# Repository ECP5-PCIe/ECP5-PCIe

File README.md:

# ECP5-PCIe

## ECP5 to PCIe interface development

The goal of this project is to provide a PCIe interface in [Amaranth HDL](https://github.com/amaranth-lang/amaranth).

## Previous work

There already exists a PCIe physical layer by whitequark called [Yumewatari](https://github.com/whitequark/Yumewatari) and a TLP and DMA layer by enjoy-digital called [litepcie](https://github.com/enjoy-digital/litepcie/tree/master/litepcie) written in omigen.

## TODO
- Read through Yumewatari and litepcie code
- Read more of the PCIe spec and summarize relevant parts
- Get an ECP5 device capable of PCIe
	- Currently an adapter for the ECP5 EVN to PCIe is being built

## INSTALL

Execute `python setup.py develop` in the Gateware folder

## SIMULATE

- Execute `python test_pcie_virtual.py` in the Tests folder to run the simulation
- Execute `gtkwave test.gtkw` to view the results

## [SETUP][wiki-setup]

See [the Setup page in the Wiki][wiki-setup]

## RUN

- Enable PCIe on the connected device (for example on the ROCKPro64 execute `pci init` in u-boot)
- Execute `python test_pcie_phy.py run` in the Tests folder to upload the gateware to the ECP5
- Execute `python test_pcie_phy.py grab` to get DLLPs received in the L0 state (and the time since it has been in the L0 state).
Sometimes the last few results are invalid and the program doesn't halt, end it by pressing `Ctrl + C`.
It should show something like this:

Data is composed of the first symbol received in one clock cycle, its representation in hexadecimal, the same for the second symbol.
The time is in clock cycles since entering L0, which are 8 ns each.

#### Time since L0 | RX data | TX data | Temperature

[wiki-setup]: https://codeberg.org/ECP5-PCIe/ECP5-PCIe/wiki/Setup

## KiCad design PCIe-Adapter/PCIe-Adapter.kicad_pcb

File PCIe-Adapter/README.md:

# ECP5 EVN to PCIe x4 adapter board
This is an adapter board for the ECP5 EVN, such that it can be used with PCIe x1 or x4. It has a PLL to double the incoming PCIe clock, since it has better jitter performance than the ones in the ECP5.
It also has an ATMega328 which is connected over UART to the ECP5 to save on interface pins and FPGA logic complexity for configuring the PLL.

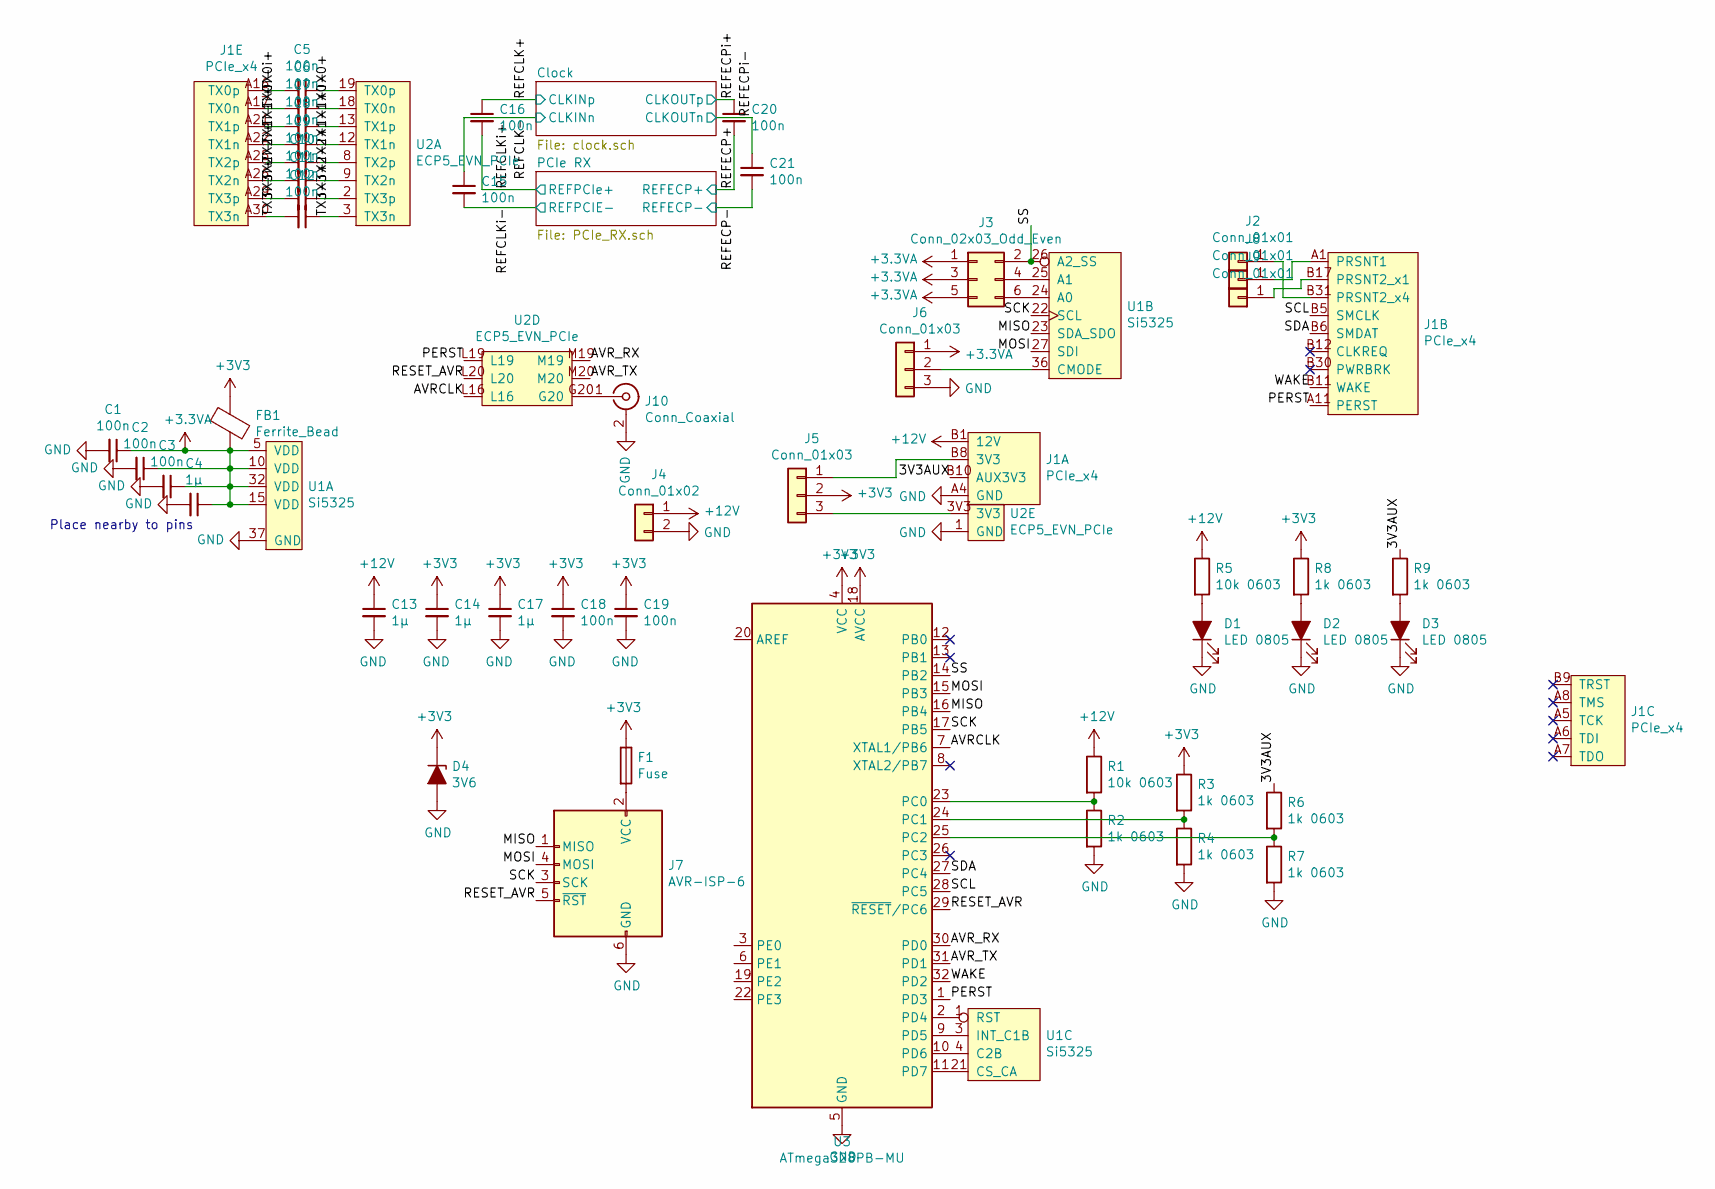
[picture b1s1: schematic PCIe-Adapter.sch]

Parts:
C1, C2, C3, C5, C6, C7, C8, C9, C10, C11, C12, C15, C16, C18, C19, C20, C21: 100n; C_0402_1005Metric
C4, C13, C14, C17: 1µ; C_0805_2012Metric
D1, D2, D3: LED 0805; LED_0805_2012Metric
D4: 3V6; D_SMB
F1: Fuse; Fuse_1206_3216Metric
FB1: Ferrite_Bead; L_0805_2012Metric
J1: PCIe_x4
J2, J8, J9: Conn_01x01; TestPoint_Pad_1.5x1.5mm
J3: Conn_02x03_Odd_Even; PinHeader_2x03_P2.54mm_Vertical
J4: Conn_01x02; PinHeader_1x02_P2.54mm_Vertical
J5, J6: Conn_01x03; PinHeader_1x03_P2.54mm_Vertical
J7: AVR-ISP-6; PinHeader_2x03_P2.54mm_Vertical
J10: Conn_Coaxial; SMA_Samtec_SMA-J-P-X-ST-EM1_EdgeMount
R1, R5: 10k 0603; R_0603_1608Metric
R2, R3, R4, R6, R7, R8, R9: 1k 0603; R_0603_1608Metric
U1: Si5325
U2: ECP5_EVN_PCIe; ECP5-EVN-PCIe
U3: ATmega328PB-MU; QFN-32-1EP_5x5mm_P0.5mm_EP3.1x3.1mm

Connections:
+3.3VA: C1.1, C2.1, C3.1, C4.1, FB1.2, J3.1, J3.3, J3.5, J6.1, U1.5 (VDD), U1.10 (VDD), U1.11 (VDD), U1.15 (VDD), U1.32 (VDD)
+3V3: C14.1, C17.1, C18.1, C19.1, D4.1 (K), F1.1, FB1.1, J5.2, R3.1, R8.1, U3.4 (VCC), U3.18 (AVCC)
+12V: C13.1, J1.A2 (12V), J1.A3 (12V), J1.B1 (12V), J1.B2 (12V), J1.B3 (12V), J4.1, R1.1, R5.1
/3V3AUX: J1.B10 (AUX3V3), R6.1, R9.1
/AVRCLK: U2.L16, U3.7 (XTAL1/PB6)
/AVR_RX: U2.M19, U3.30 (PD0)
/AVR_TX: U2.M20, U3.31 (PD1)
/MISO: J7.1 (MISO), U1.23 (SDA_SDO), U3.16 (PB4)
/MOSI: J7.4 (MOSI), U1.27 (SDI), U3.15 (PB3)
/PERST: J1.A11 (PERST), U2.L19, U3.1 (PD3)
/REFCLK+: C16.1; also elsewhere on the board
/REFCLK-: C15.1; also elsewhere on the board
/REFCLKi+: C16.2; also elsewhere on the board
/REFCLKi-: C15.2; also elsewhere on the board
/REFECP+: C20.2; also elsewhere on the board
/REFECP-: C21.2; also elsewhere on the board
/REFECPi+: C20.1; also elsewhere on the board
/REFECPi-: C21.1; also elsewhere on the board
/RESET_AVR: J7.5 (~RST), U2.L20, U3.29 (~RESET~/PC6)
/SCK: J7.3 (SCK), U1.22 (SCL), U3.17 (PB5)
/SCL: J1.B5 (SMCLK), U3.28 (PC5)
/SDA: J1.B6 (SMDAT), U3.27 (PC4)
/SS: J3.2, U1.26 (A2_SS), U3.14 (PB2)
/TX0+: C5.1, U2.19 (TX0p)
/TX0-: C6.1, U2.18 (TX0n)
/TX0i+: C5.2, J1.A16 (TX0p)
/TX0i-: C6.2, J1.A17 (TX0n)
/TX1+: C7.1, U2.13 (TX1p)
/TX1-: C8.1, U2.12 (TX1n)
/TX1i+: C7.2, J1.A21 (TX1p)
/TX1i-: C8.2, J1.A22 (TX1n)
/TX2+: C9.1, U2.8 (TX2p)
/TX2-: C10.1, U2.9 (TX2n)
/TX2i+: C9.2, J1.A25 (TX2p)
/TX2i-: C10.2, J1.A26 (TX2n)
/TX3+: C11.1, U2.2 (TX3p)
/TX3-: C12.1, U2.3 (TX3n)
/TX3i+: C11.2, J1.A29 (TX3p)
/TX3i-: C12.2, J1.A30 (TX3n)
/WAKE: J1.B11 (WAKE), U3.32 (PD2)
GND: C1.2, C2.2, C3.2, C4.2, C13.2, C14.2, C17.2, C18.2, C19.2, D1.1 (K), D2.1 (K), D3.1 (K), D4.2 (A), J1.A4 (GND), J1.A12 (GND), J1.A15 (GND), J1.A18 (GND), J1.A20 (GND), J1.A23 (GND), J1.A24 (GND), J1.A27 (GND), J1.A28 (GND), J1.A31 (GND), J1.B4 (GND), J1.B7 (GND), J1.B13 (GND), J1.B16 (GND), J1.B18 (GND), J1.B21 (GND), J1.B22 (GND), J1.B25 (GND), J1.B26 (GND), J1.B29 (GND), J1.B32 (GND), J4.2, J6.3, J7.6 (GND), J10.2 (Ext), R2.2, R4.2, R7.2, U1.6 (GND), U1.8 (GND), U1.19 (GND), U1.20 (GND), U1.31 (GND), U1.37 (GND), U2.1 (GND), U3.5 (GND), U3.21 (GND), U3.33 (GND)
unnamed: D1.2 (A), R5.2
unnamed: D2.2 (A), R8.2
unnamed: D3.2 (A), R9.2
unnamed: F1.2, J7.2 (VCC)
unnamed: J1.A1 (PRSNT1), J8.1
unnamed: J1.A9 (3V3), J1.A10 (3V3), J1.B8 (3V3), J5.1
unnamed: J1.B17 (PRSNT2_x1), J9.1
unnamed: J1.B31 (PRSNT2_x4), J2.1
unnamed: J3.4, U1.25 (A1)
unnamed: J3.6, U1.24 (A0)
unnamed: J5.3, U2.3V3
unnamed: J6.2, U1.36 (CMODE)
unnamed: J10.1 (In), U2.G20
unnamed: R1.2, R2.1, U3.23 (PC0)
unnamed: R3.2, R4.1, U3.24 (PC1)
unnamed: R6.2, R7.1, U3.25 (PC2)
unnamed: U1.1 (RST), U3.2 (PD4)
unnamed: U1.3 (INT_C1B), U3.9 (PD5)
unnamed: U1.4 (C2B), U3.10 (PD6)
unnamed: U1.21 (CS_CA), U3.11 (PD7)

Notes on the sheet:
Place nearby to pins

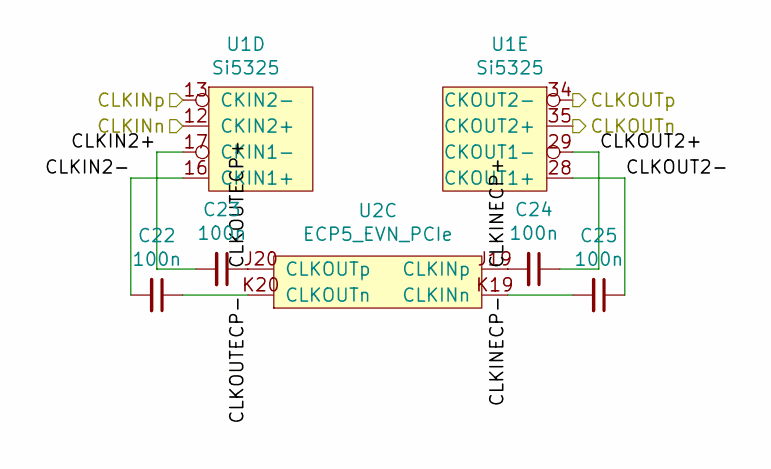
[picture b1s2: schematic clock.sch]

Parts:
C22, C23, C24, C25: 100n; C_0402_1005Metric
U1: Si5325
U2: ECP5_EVN_PCIe

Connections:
/Clock/CLKIN2+: C23.2, U1.17 (CKIN1-)
/Clock/CLKIN2-: C22.2, U1.16 (CKIN1+)
/Clock/CLKINECP+: C24.2, U2.J19 (CLKINp)
/Clock/CLKINECP-: C25.2, U2.K19 (CLKINn)
/Clock/CLKOUT2+: C24.1, U1.29 (CKOUT1-)
/Clock/CLKOUT2-: C25.1, U1.28 (CKOUT1+)
/Clock/CLKOUTECP+: C23.1, U2.J20 (CLKOUTp)
/Clock/CLKOUTECP-: C22.1, U2.K20 (CLKOUTn)
/REFCLK+: U1.13 (CKIN2-); also elsewhere on the board
/REFCLK-: U1.12 (CKIN2+); also elsewhere on the board
/REFECPi+: U1.34 (CKOUT2-); also elsewhere on the board
/REFECPi-: U1.35 (CKOUT2+); also elsewhere on the board

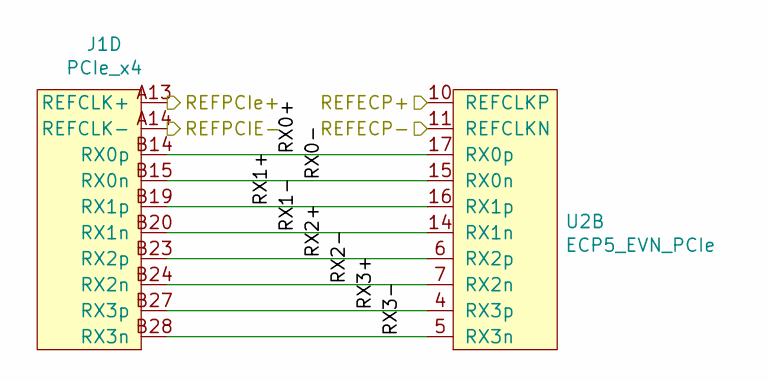
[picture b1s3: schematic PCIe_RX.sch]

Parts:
J1: PCIe_x4
U2: ECP5_EVN_PCIe

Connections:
/PCIe RX/RX0+: J1.B14 (RX0p), U2.17 (RX0p)
/PCIe RX/RX0-: J1.B15 (RX0n), U2.15 (RX0n)
/PCIe RX/RX1+: J1.B19 (RX1p), U2.16 (RX1p)
/PCIe RX/RX1-: J1.B20 (RX1n), U2.14 (RX1n)
/PCIe RX/RX2+: J1.B23 (RX2p), U2.6 (RX2p)
/PCIe RX/RX2-: J1.B24 (RX2n), U2.7 (RX2n)
/PCIe RX/RX3+: J1.B27 (RX3p), U2.4 (RX3p)
/PCIe RX/RX3-: J1.B28 (RX3n), U2.5 (RX3n)
/REFCLKi+: J1.A13 (REFCLK+); also elsewhere on the board
/REFCLKi-: J1.A14 (REFCLK-); also elsewhere on the board
/REFECP+: U2.10 (REFCLKP); also elsewhere on the board
/REFECP-: U2.11 (REFCLKN); also elsewhere on the board

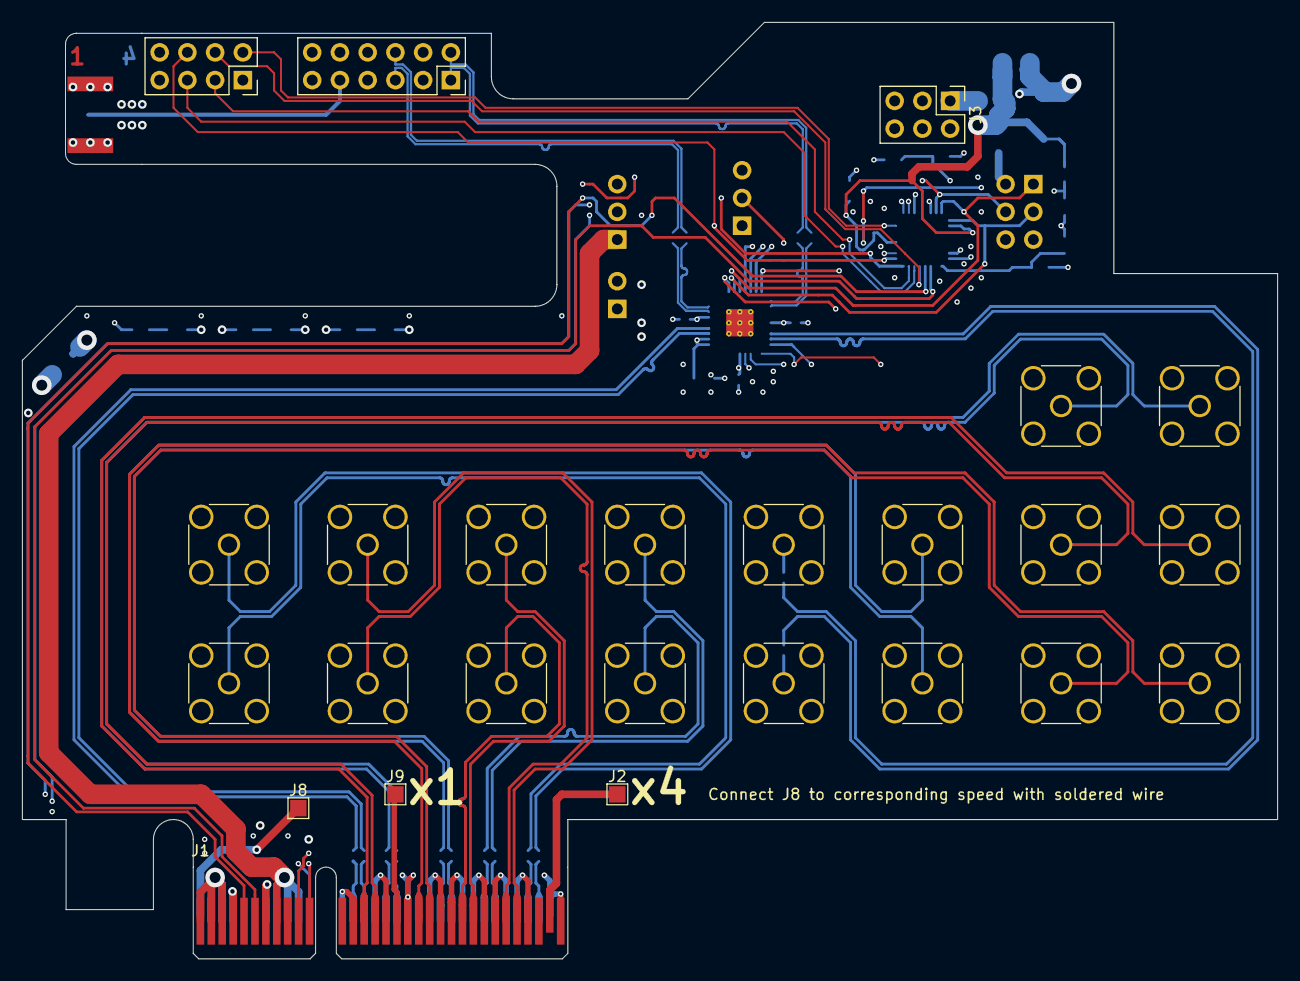
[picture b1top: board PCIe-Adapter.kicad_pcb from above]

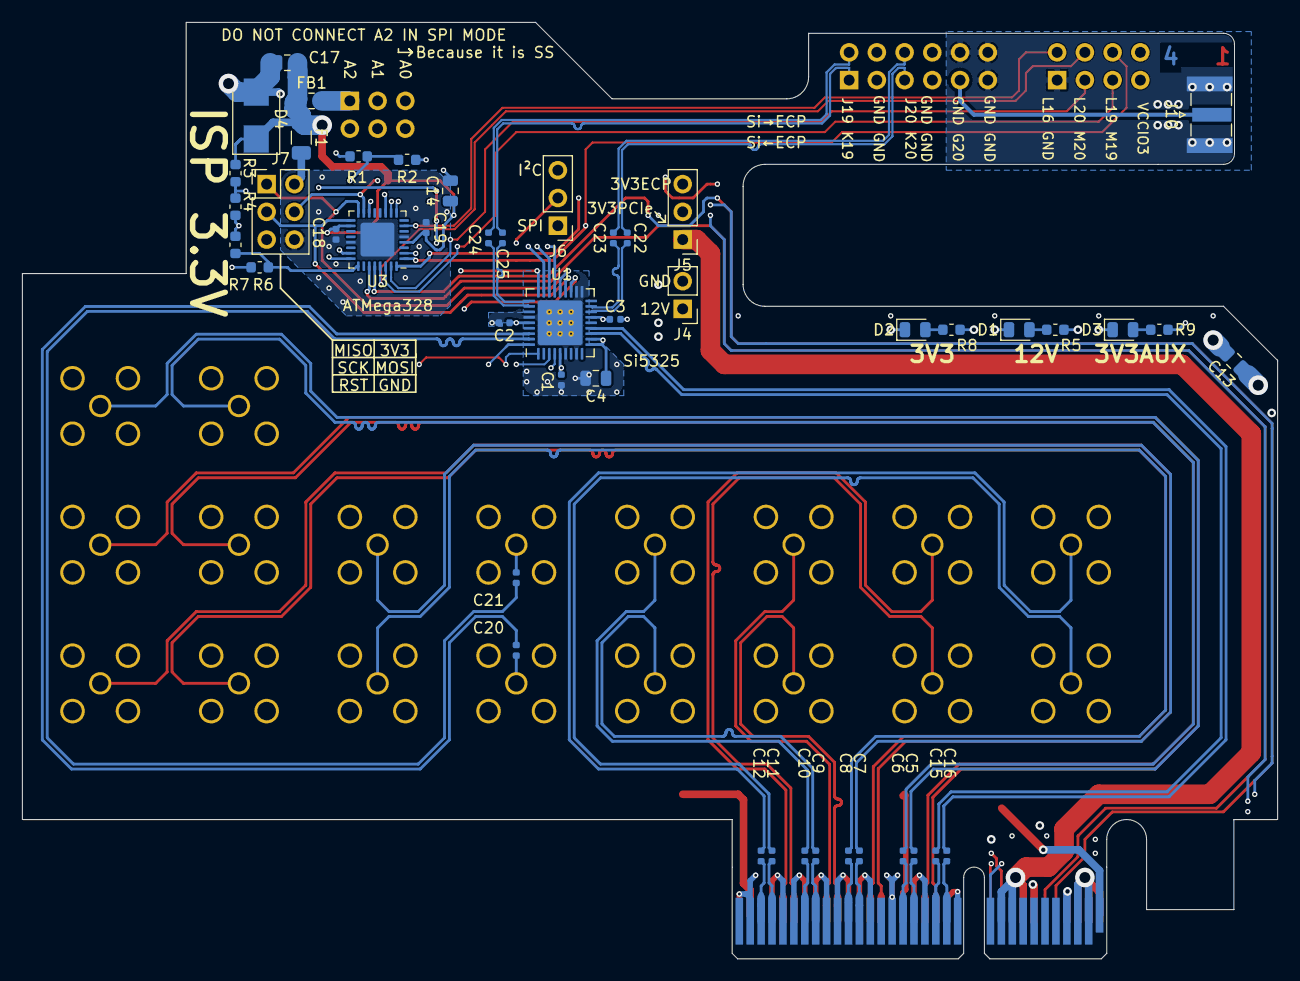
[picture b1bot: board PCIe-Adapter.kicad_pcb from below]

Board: 4 copper layers, 115.0 x 85.8 mm, 53 parts (47 on the bottom side), 77 nets.

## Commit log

2020-03-30 init
2020-04-04 images
2020-05-12 PCIe adapter board implementation
2020-05-15 ATMega programmer and basic code for it, 16 MHz clock generator and UART passthrough, PLL diff pairs added
2020-05-16 PLL testing
2020-05-29 serdes from Yumewatari
2020-05-31 oscg test
2020-05-31 fixed attrs
2020-06-03 serdes added
2020-06-03 fixed serdes, started work on test
2020-06-07 added debug reader
2020-06-07 working pcie symbol recovery
2020-06-08 nmigen yumewatari
2020-06-08 changed serdes to use lane
2020-06-08 x2 working, COM aligned to first word
2020-06-08 TSn state machine implemented for testing
2020-06-08 fixed link and lane signals
2020-06-08 docs
2020-06-11 FSM now in rx class, started work on LTSSM
2020-06-13 ltssm state machine implementation has begun
2020-06-16 further work on ltssm
2020-06-18 comments
2020-06-18 ltssm fsm now with enum
2020-06-18 LTSSM comments
2020-06-20 comments and python package
2020-06-20 tests
2020-06-21 timer fixed, added state names to debug ltssm
2020-06-21 everything in rx clock domain
2020-06-24 tx test case
2020-06-26 comments and more debug
2020-06-26 ltssm bugfixes
2020-07-01 ltssm fixes
2020-07-10 upload gateware and rx/tx phase testing
2020-07-16 phy testing
2020-07-17 serdes testing
2020-07-20 RockPRO64 pcie init, begun implementation of that
2020-07-22 RockPRO64 preliminary
2020-07-22 bypass 8b10b
2020-07-22 serdes tests
2020-07-23 disabled word alignment
2020-07-25 ROCKPro64 PCIe init automation
2020-07-26 serdes decoding enabled, some more testing
2020-07-28 testing done
2020-07-29 fixed issue in rx_has_symbol and SERDES and moved CDC to PCIeSERDESAligner
2020-07-31 fixed tx
2020-07-31 add SKP ordered sets to TX and fix ROCKPro64 pci init
2020-07-31 SKP ordered set TX fix
2020-08-01 fixed serdes issue
2020-08-04 fixed serdes rx
2020-08-06 ltssm testing
2020-08-06 fixed RX inversion issue
2020-08-06 CDC variants for testing
2020-08-10 PHY fixes
2020-08-14 x2 soft gearing
2020-08-14 ltssm test changed to soft gearing
2020-08-17 changed CH1 to CH0
2020-08-17 disabled scrambling
2020-08-18 added lfsr
2020-08-19 (de)scrambling working, LTSSM gets to L0
2020-08-20 L0 goes to recovery now
2020-08-20 PHY mostly done
2020-08-20 added to readme that the reading program sometimes doesnt halt
2020-08-25 added DLLP receiver
2020-08-28 added DCU and channel configuration as constructor parameters
2020-08-31 SERDES DCU and channel configuration
2020-09-01 added DLLP transmitter and fixed an inconsequential thing in the TX phy
2020-09-01 phy now configured such that it loops back DLLPs, to show that DLLP receiver and transmitter are working
2020-09-28 DLL credit transmission working
2020-09-29 fixed SERDES gearing and improved Data Link Layer
2020-10-15 x4 SERDES
2020-10-15 increased speed of x4 SERDES
2020-10-15 cleaned up serdes x4 test and fixed bug in serdes
2020-10-20 add ispCLOCK configurations and provide signal to switch to 5 GT/s
2020-10-20 saved ispCLOCK.md contents and moved it to the ispCLOCK folder
2020-10-20 fixed SERDES clocking issue by fixing the reset
2020-10-30 LTSSM works in x4 width
2020-11-01 x4 DLL working
2020-11-01 Add temperature to test_pcie_phy.py and set speed_5GTps true in the example and fix the SERDES to default to 2.5 GT/s even if that is enabled
2020-11-01 increased TX and RX gearing speed
2020-11-03 Added speed switching support for relevant classes (not in LTSSM yet) and fixed ispCLOCK configs
2020-11-03 fixed timing
2020-11-03 add reset
2020-11-03 added second UARTDebugger and fixed dll
2020-11-03 removed PCIe detection from LTSSM since it didn't work anyways
2020-11-03 improved reset a little
2021-04-03 Added SCI interface and a few other things being worked on in the last months
2021-04-03 ignore vscode
2021-04-03 Fixed bug in SCI
2021-04-03 Fixed comment
2021-08-05 virtual simulations, SERDES improvements
2021-08-05 made DLLP variable naming better
2021-08-05 updated README.md for simulation
2021-08-05 moved simulate in README.md up
2021-10-21 added test TLP generator and fixed CRC
2021-11-21 Add CRC test and fix LCRC generation
2021-12-04 add 'compose' function to serdes.py and improve comments and fix bug in phy_rx.py which caused the idle signal to go low when receiving an SKP ordered set which caused the LTSSM to reset
2021-12-05 Add TLP buffer
2021-12-05 Fix some bugs with the TLPBuffer and rename from RetryBuffer to TLPBuffer
2021-12-12 fixed memory
2021-12-12 change to amaranth
2021-12-12 remove lockfile
2021-12-12 Moved TLP transmitter into a FSM
2021-12-12 Add documentation flowchart
2021-12-12 Added Ack and Nak
2021-12-17 Add configuration memory
2021-12-20 Disable RX equalizer and a few other bugfixes
2021-12-20 Fix 5 GT/s speed and fix SKP TX time
2021-12-20 Compile flowchart as SVG and link new Wiki
2022-02-19 Add onboard refclk in case host doesn't provide a refclk
2022-06-27 A lot of updates
2022-12-26 More tests
2023-01-14 Add PCIe receiver detection, amongst other things
2023-02-18 Added VariableLogger
2023-05-16 Latest changes
